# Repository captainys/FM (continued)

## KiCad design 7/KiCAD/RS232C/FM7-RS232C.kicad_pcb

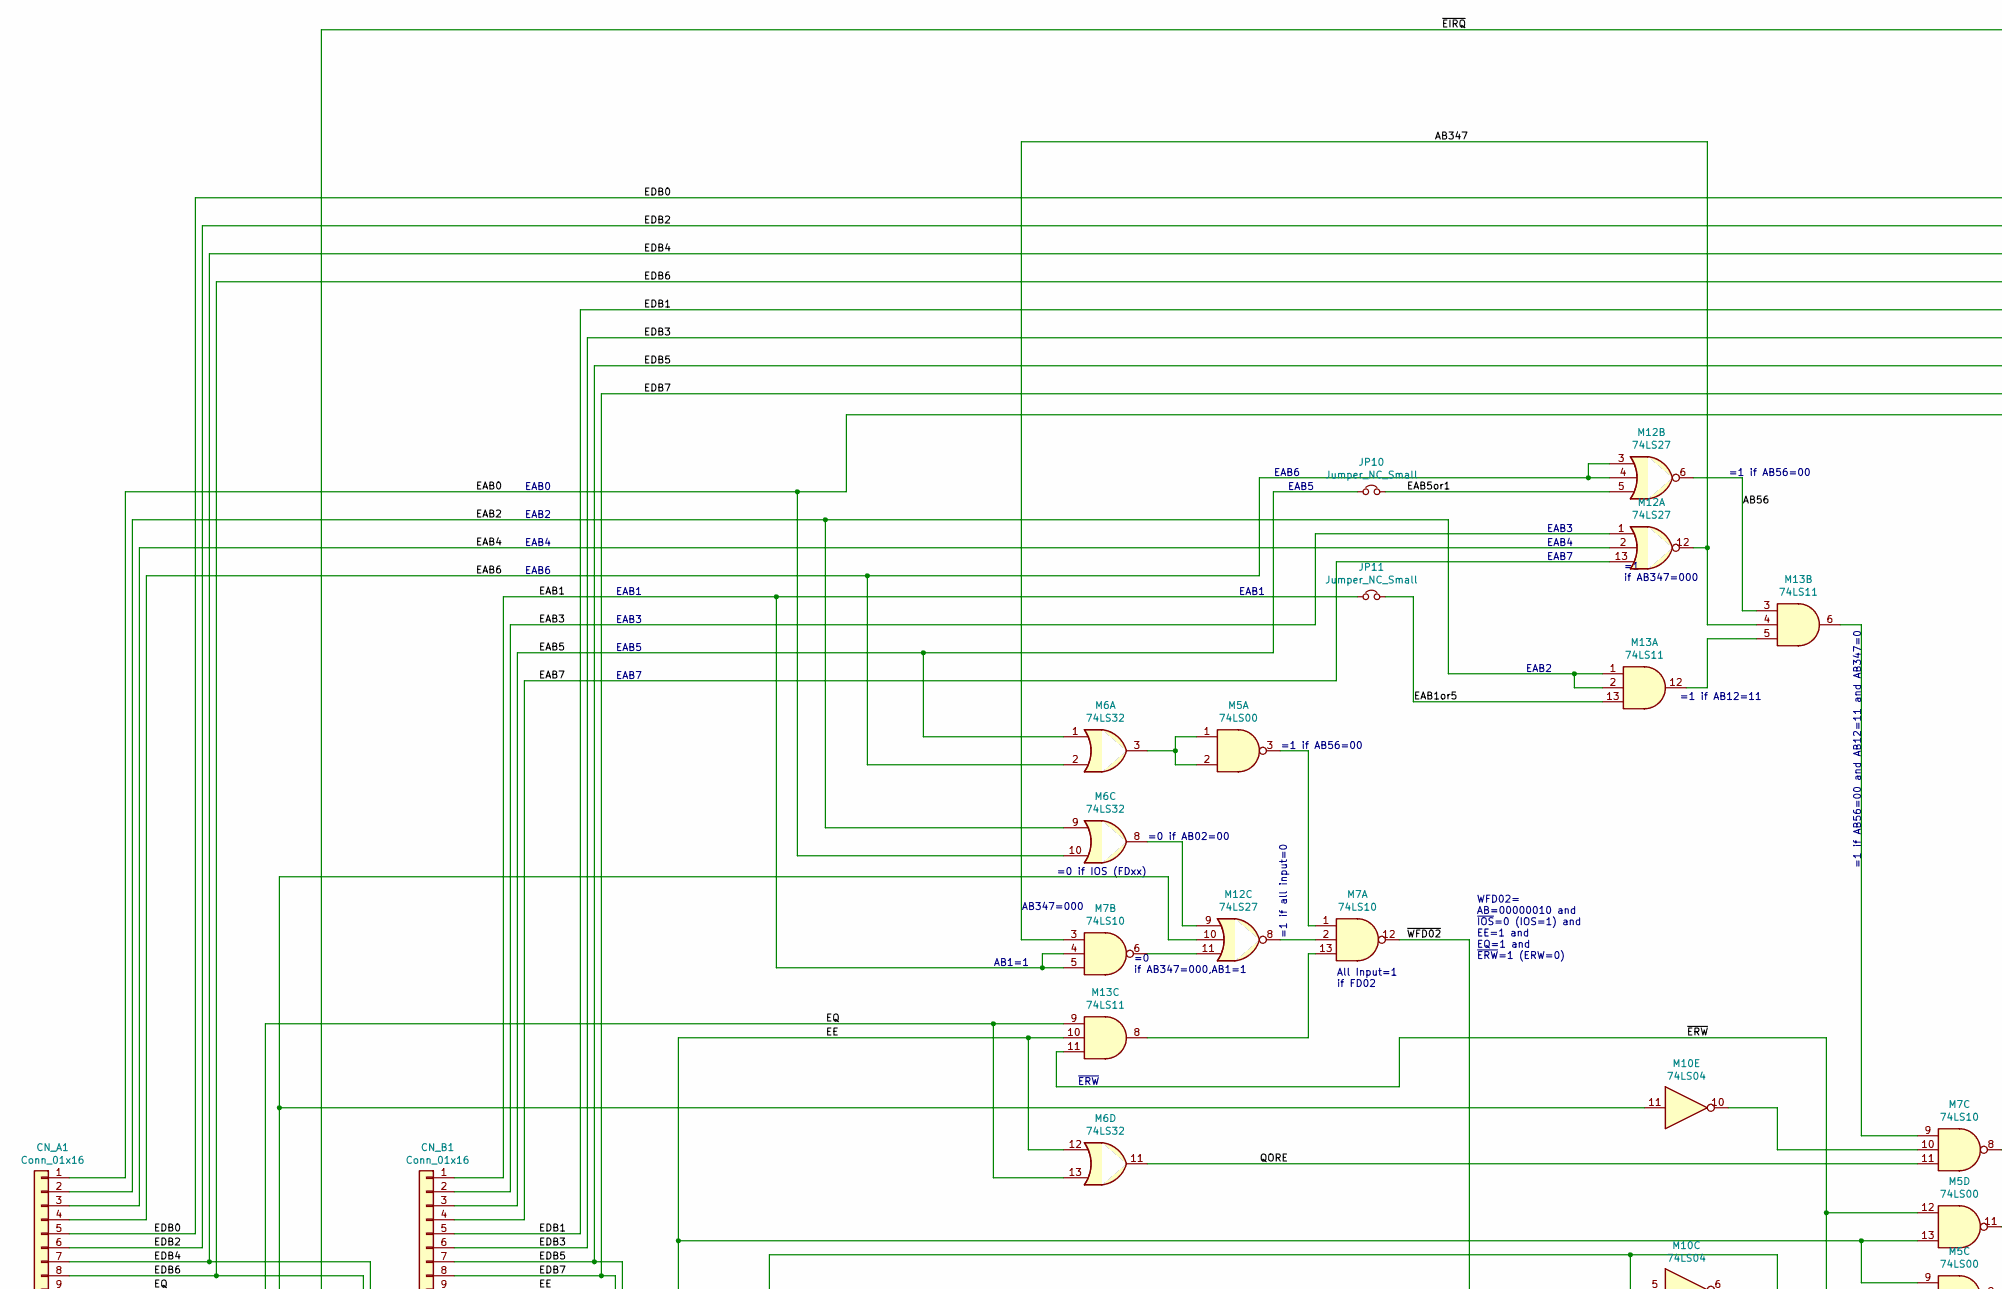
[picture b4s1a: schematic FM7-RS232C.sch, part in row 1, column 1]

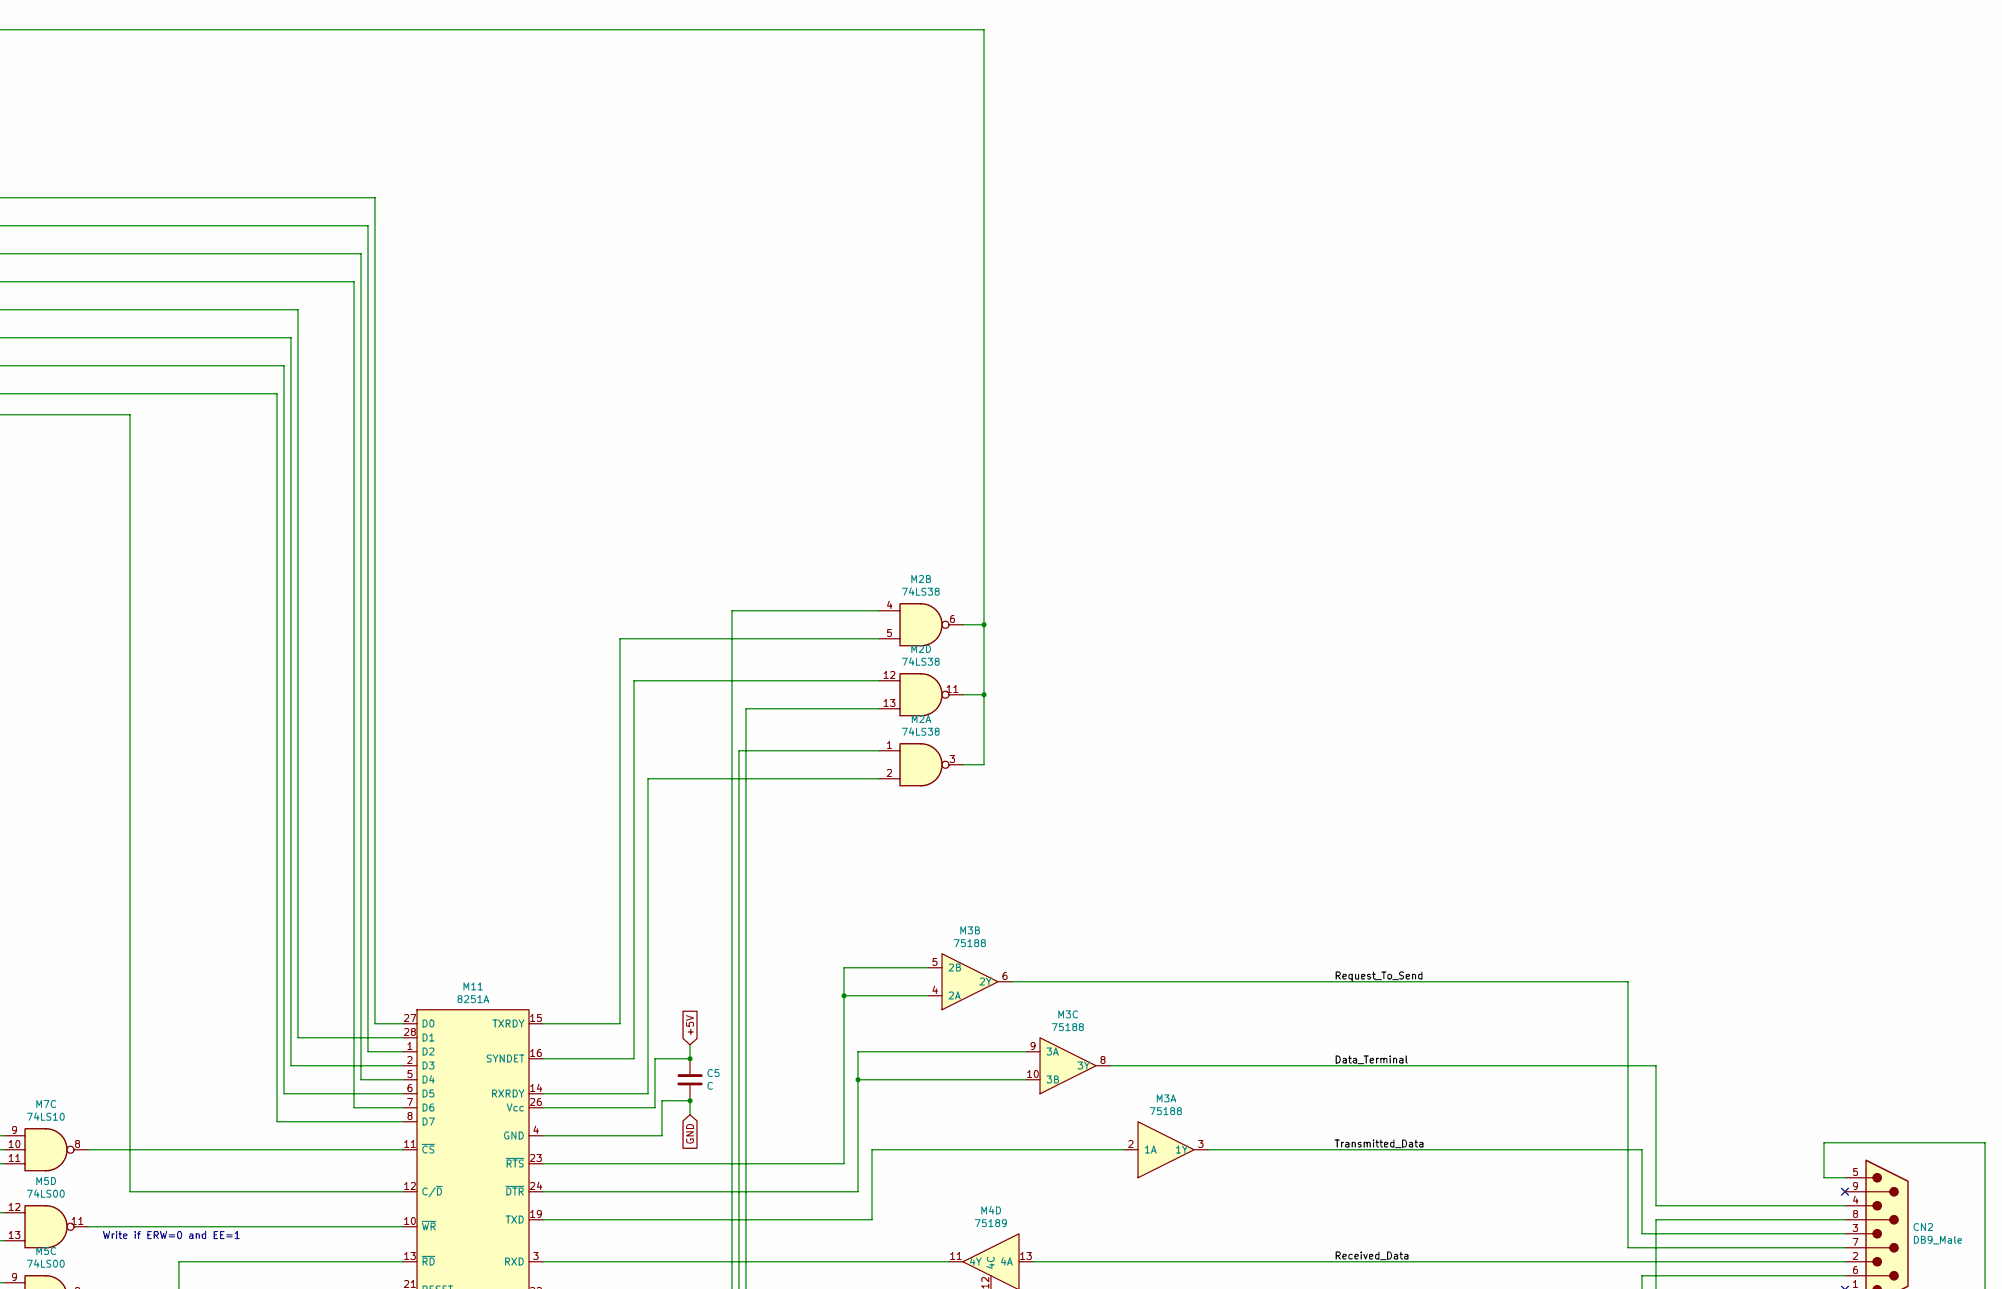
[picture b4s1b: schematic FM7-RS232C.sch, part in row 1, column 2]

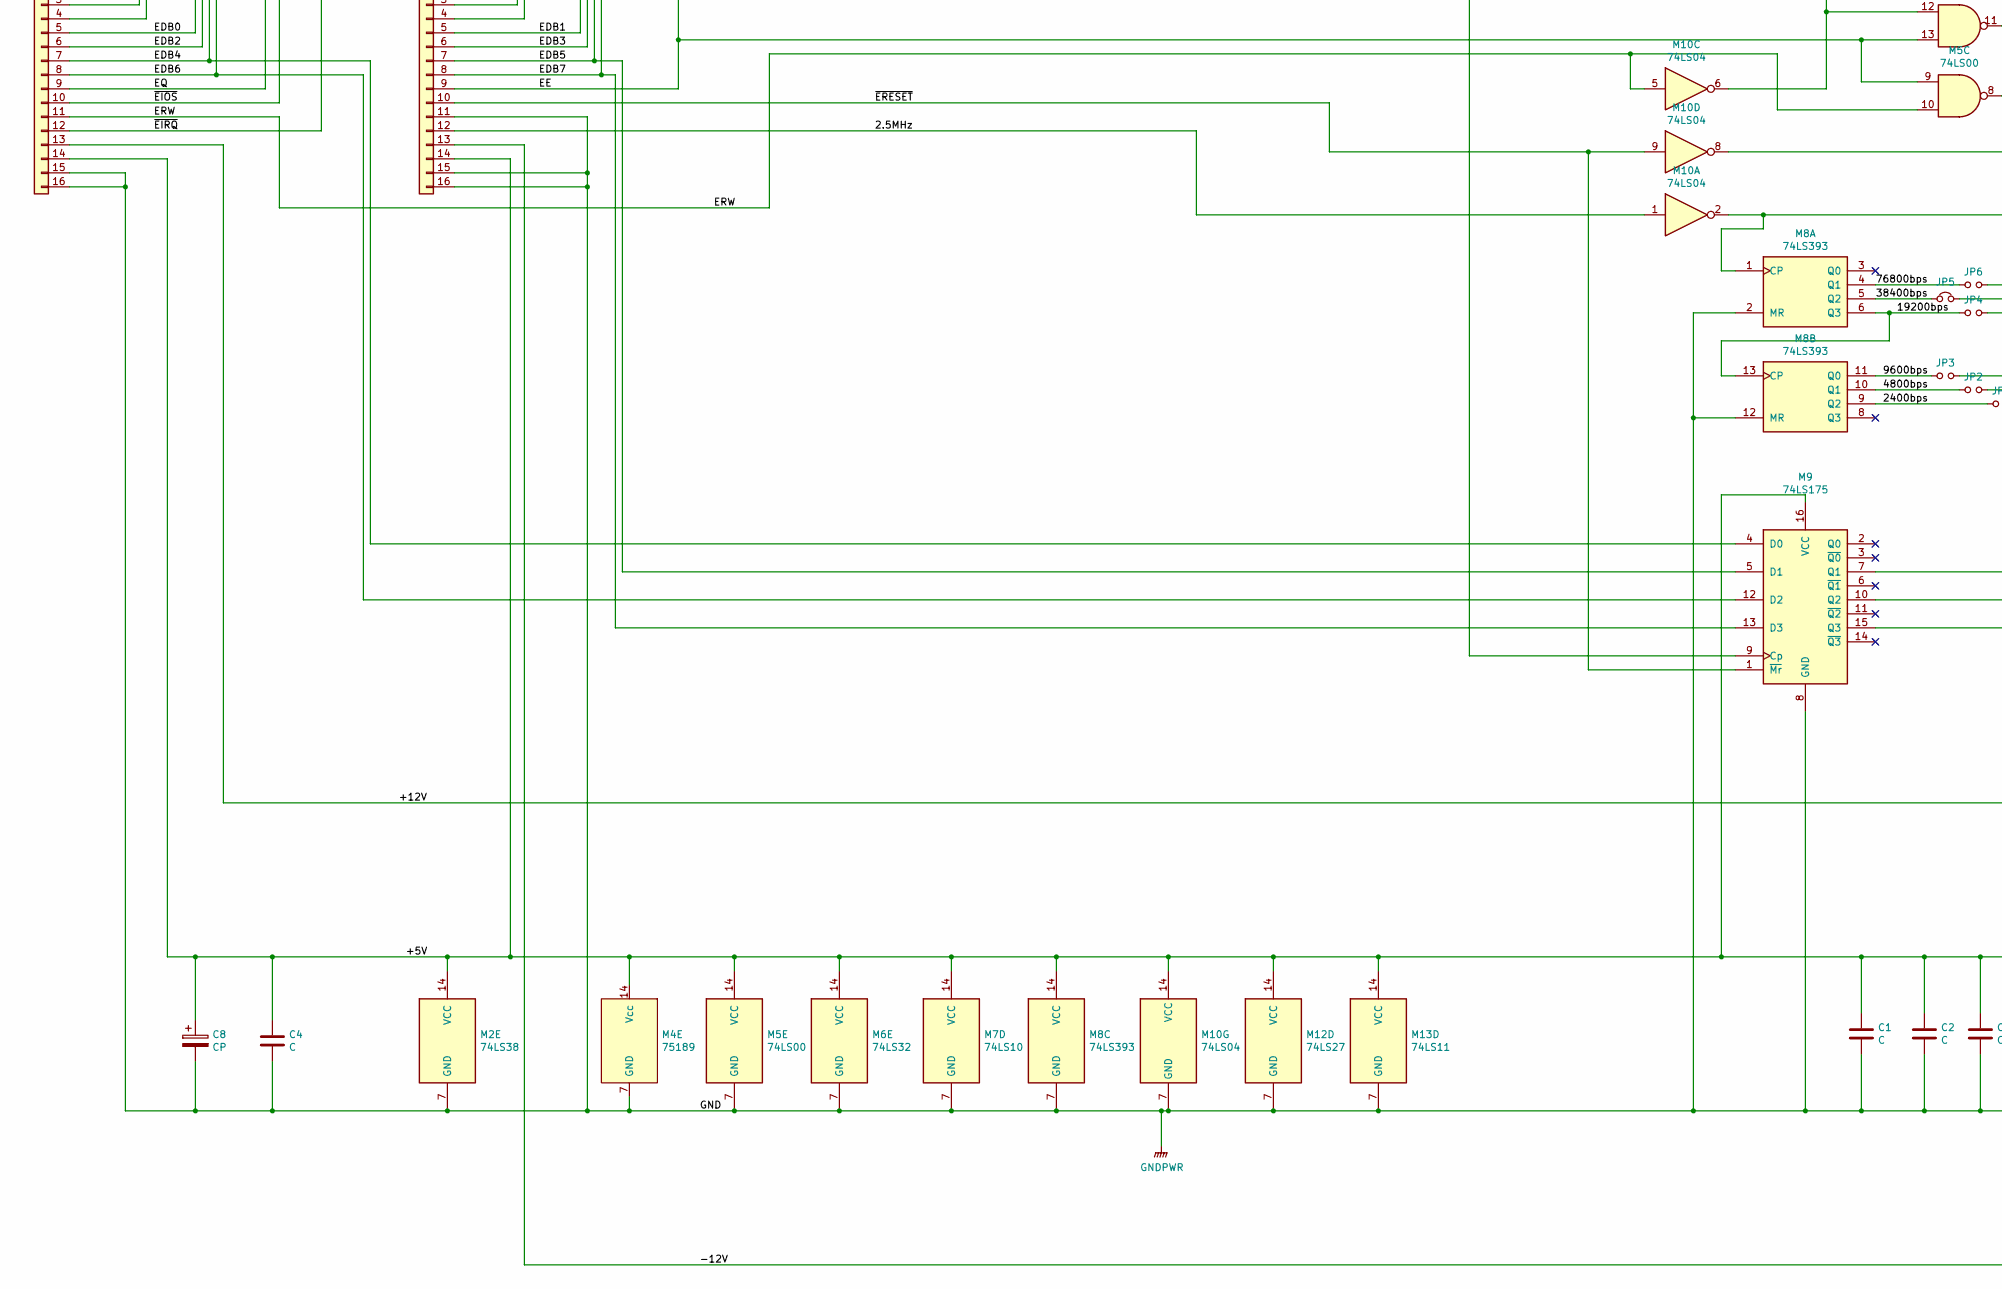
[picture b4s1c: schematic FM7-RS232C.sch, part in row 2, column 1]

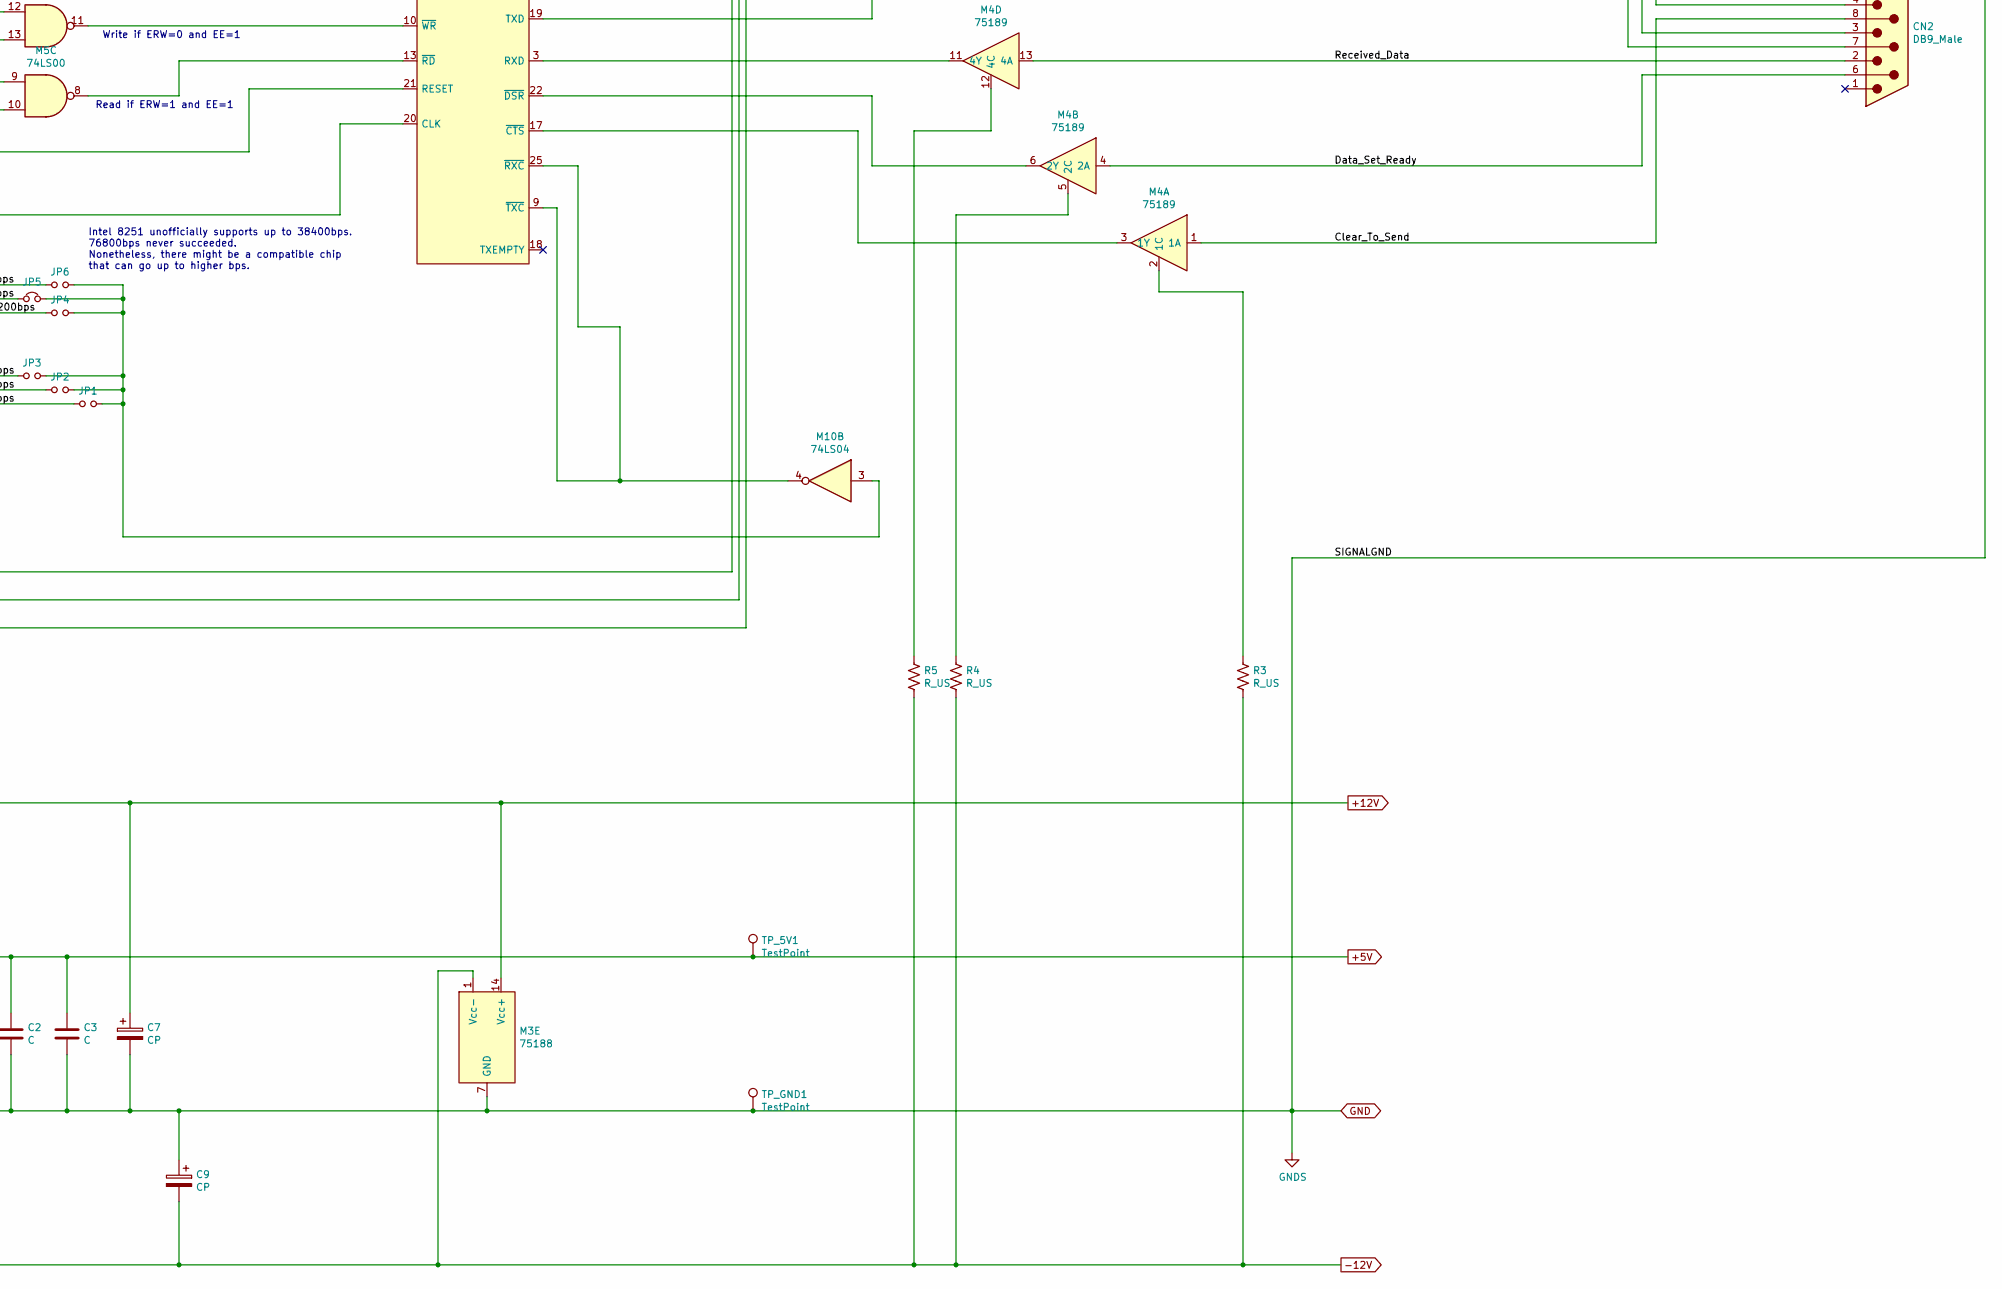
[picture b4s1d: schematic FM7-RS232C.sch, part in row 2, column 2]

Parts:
C1, C2, C3, C4, C5: C; C_Disc_D7.5mm_W5.0mm_P7.50mm
C7, C8, C9: CP; C_Axial_L17.0mm_D6.5mm_P25.00mm_Horizontal
CN2: DB9_Male; DSUB-9_Male_Vertical_P2.77x2.84mm
CN_A1: Conn_01x16; PinHeader_1x16_P2.54mm_Vertical
CN_B1: Conn_01x16; PinHeader_1x16_P2.54mm_Vertical
JP1, JP2, JP3, JP4, JP6: Jumper_NO_Small; PinHeader_1x02_P2.54mm_Vertical
JP5, JP10, JP11: Jumper_NC_Small; PinHeader_1x02_P2.54mm_Vertical
M2: 74LS38; DIP-14_W7.62mm_Socket
M3: 75188; DIP-14_W7.62mm_Socket
M4: 75189; DIP-14_W7.62mm_Socket
M5: 74LS00; DIP-14_W7.62mm_Socket
M6: 74LS32
M7: 74LS10; DIP-14_W7.62mm_Socket
M8: 74LS393; DIP-14_W7.62mm_Socket
M9: 74LS175; DIP-16_W7.62mm_Socket
M10: 74LS04; DIP-14_W7.62mm_Socket
M11: 8251A; DIP-28_W15.24mm_Socket
M12: 74LS27; DIP-14_W7.62mm_Socket
M13: 74LS11; DIP-14_W7.62mm_Socket
R3, R4, R5: R_US; R_Axial_DIN0207_L6.3mm_D2.5mm_P10.16mm_Horizontal
TP_5V1: TestPoint; TestPoint_THTPad_D1.5mm_Drill0.7mm
TP_GND1: TestPoint; TestPoint_THTPad_D1.5mm_Drill0.7mm

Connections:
+5V: C1.1, C2.1, C3.1, C4.1, C5.1, C8.1, CN_A1.14, CN_B1.14, M2.14 (VCC), M4.14 (Vcc), M5.14 (VCC), M6.14 (VCC), M7.14 (VCC), M8.14 (VCC), M9.16 (VCC), M10.14 (VCC), M11.26 (Vcc), M12.14 (VCC), M13.14 (VCC), TP_5V1.1
+12V: C7.1, CN_A1.13, M3.14 (Vcc+)
-12V: C9.2, CN_B1.13, M3.1 (Vcc-), R3.2, R4.2, R5.2
/2.5MHz: CN_B1.12, M10.1
/2400bps: JP1.1, M8.9 (Q2)
/4800bps: JP2.1, M8.10 (Q1)
/9600bps: JP3.1, M8.11 (Q0)
/19200bps: JP4.1, M8.6 (Q3), M8.13 (CP)
/38400bps: JP5.1, M8.5 (Q2)
/76800bps: JP6.1, M8.4 (Q1)
/AB56: M12.6, M13.3
/AB347: M7.3, M12.12, M13.4
/Clear_To_Send: CN2.8, M4.1 (1A)
/Data_Set_Ready: CN2.6, M4.4 (2A)
/Data_Terminal: CN2.4, M3.8 (3Y)
/EAB0: CN_A1.1, M6.10, M11.12 (C/~D)
/EAB1: CN_B1.1, JP11.1, M7.4, M7.5
/EAB1or5: JP11.2, M13.13
/EAB2: CN_A1.2, M6.9, M13.1, M13.2
/EAB3: CN_B1.2, M12.1
/EAB4: CN_A1.3, M12.2
/EAB5: CN_B1.3, JP10.1, M6.1
/EAB5or1: JP10.2, M12.5
/EAB6: CN_A1.4, M6.2, M12.3, M12.4
/EAB7: CN_B1.4, M12.13
/EDB0: CN_A1.5, M11.27 (D0)
/EDB1: CN_B1.5, M11.28 (D1)
/EDB2: CN_A1.6, M11.1 (D2)
/EDB3: CN_B1.6, M11.2 (D3)
/EDB4: CN_A1.7, M9.4 (D0), M11.5 (D4)
/EDB5: CN_B1.7, M9.5 (D1), M11.6 (D5)
/EDB6: CN_A1.8, M9.12 (D2), M11.7 (D6)
/EDB7: CN_B1.8, M9.13 (D3), M11.8 (D7)
/EE: CN_B1.9, M5.9, M5.13, M6.12, M13.10
/EQ: CN_A1.9, M6.13, M13.9
/ERW: CN_A1.11, M5.10, M10.5
/QORE: M6.11, M7.11
/Received_Data: CN2.2, M4.13 (4A)
/Request_To_Send: CN2.7, M3.6 (2Y)
/Transmitted_Data: CN2.3, M3.3 (1Y)
/~EIOS: CN_A1.10, M10.11, M12.10
/~EIRQ: CN_A1.12, M2.3, M2.6, M2.11
/~ERESET: CN_B1.10, M9.1 (~Mr), M10.9
/~ERW: M5.12, M10.6, M13.11
/~WFD02: M7.12, M9.9 (Cp)
GND: C1.2, C2.2, C3.2, C4.2, C5.2, C7.2, C8.2, C9.1, CN2.5, CN_A1.15, CN_A1.16, CN_B1.11, CN_B1.15, CN_B1.16, M2.7 (GND), M3.7 (GND), M4.7 (GND), M5.7 (GND), M6.7 (GND), M7.7 (GND), M8.2 (MR), M8.7 (GND), M8.12 (MR), M9.8 (GND), M10.7 (GND), M11.4 (GND), M12.7 (GND), M13.7 (GND), TP_GND1.1
unnamed: JP1.2, JP2.2, JP3.2, JP4.2, JP5.2, JP6.2, M10.3
unnamed: M2.1, M9.10 (Q2)
unnamed: M2.4, M9.7 (Q1)
unnamed: M2.13, M9.15 (Q3)
unnamed: M4.2 (1C), R3.1
unnamed: M4.5 (2C), R4.1
unnamed: M4.12 (4C), R5.1
unnamed: M5.1, M5.2, M6.3
unnamed: M5.3, M7.1
unnamed: M8.1 (CP), M10.2, M11.20 (CLK)
unnamed: M10.4, M11.9 (~TXC), M11.25 (~RXC)
unnamed: M10.8, M11.21 (RESET)
unnamed: M7.10, M10.10
unnamed: M4.11 (4Y), M11.3 (RXD)
unnamed: M5.11, M11.10 (~WR)
unnamed: M7.8, M11.11 (~CS)
unnamed: M5.8, M11.13 (~RD)
unnamed: M2.2, M11.14 (RXRDY)
unnamed: M2.5, M11.15 (TXRDY)
unnamed: M2.12, M11.16 (SYNDET)
unnamed: M4.3 (1Y), M11.17 (~CTS)
unnamed: M3.2 (1A), M11.19 (TXD)
unnamed: M4.6 (2Y), M11.22 (~DSR)
unnamed: M3.4 (2A), M3.5 (2B), M11.23 (~RTS)
unnamed: M3.9 (3A), M3.10 (3B), M11.24 (~DTR)
unnamed: M7.2, M12.8
unnamed: M6.8, M12.9
unnamed: M7.6, M12.11
unnamed: M7.9, M13.6
unnamed: M7.13, M13.8
unnamed: M13.5, M13.12

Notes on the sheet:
EAB0
EAB2
EAB4
EAB6
EAB1
EAB3
EAB5
EAB7
AB347=000
AB1=1
=0 if AB02=00
=0 if IOS (FDxx)
All Input=1 if FD02
=1 if AB56=00
=1 if AB347=000
=1 if AB12=11
=1 if all input=0
=1 if AB56=00 and AB12=11 and AB347=0
WFD02= AB=00000010 and ~IOS~=0 (IOS=1) and EE=1 and EQ=1 and ~ERW~=1 (ERW=0)
Read if ERW=1 and EE=1
Write if ERW=0 and EE=1
Intel 8251 unofficially supports up to 38400bps. 76800bps never succeeded. Nonetheless, there might be a compatible chip that can go up to higher bps.
=0 if AB347=000,AB1=1
~ERW

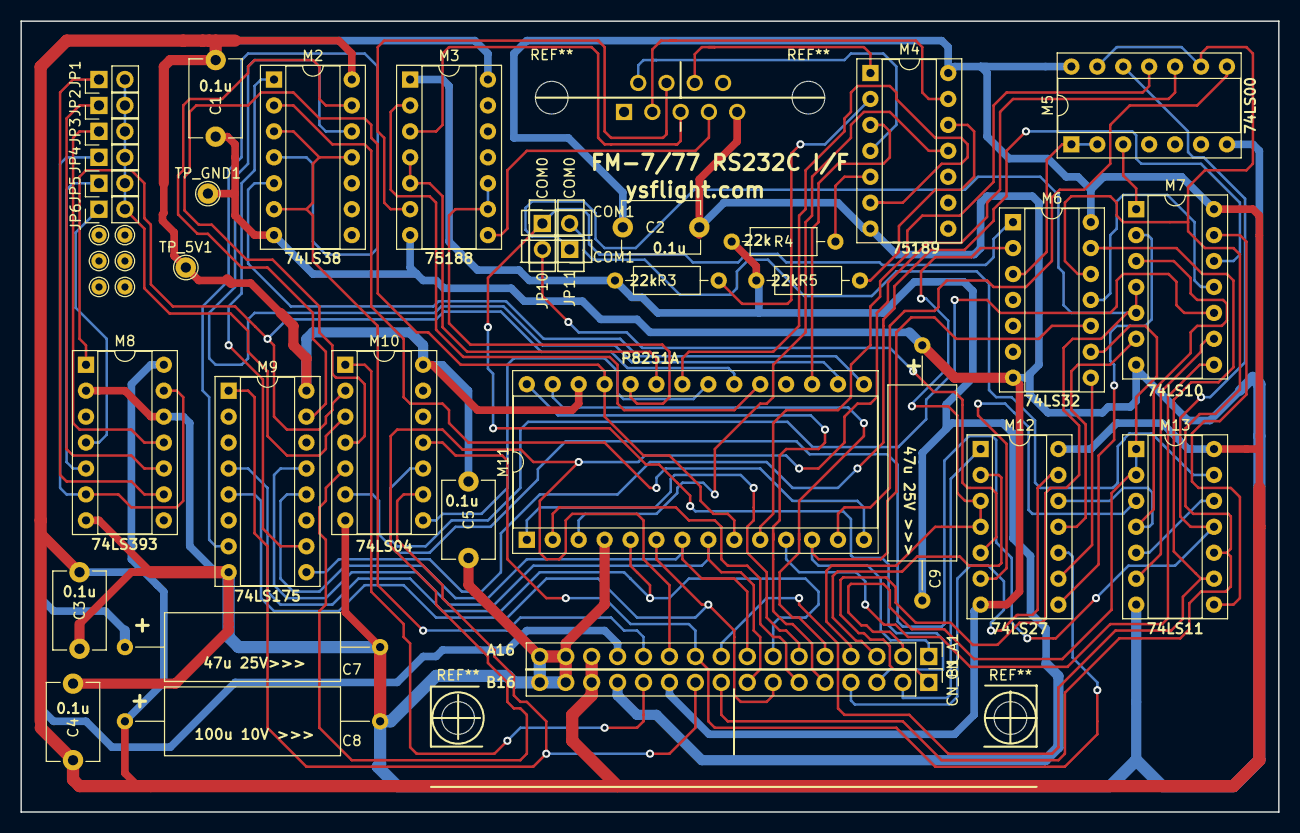
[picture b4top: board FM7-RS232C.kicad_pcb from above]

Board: 2 copper layers, 123.2 x 77.5 mm, 36 parts (1 on the bottom side), 77 nets.

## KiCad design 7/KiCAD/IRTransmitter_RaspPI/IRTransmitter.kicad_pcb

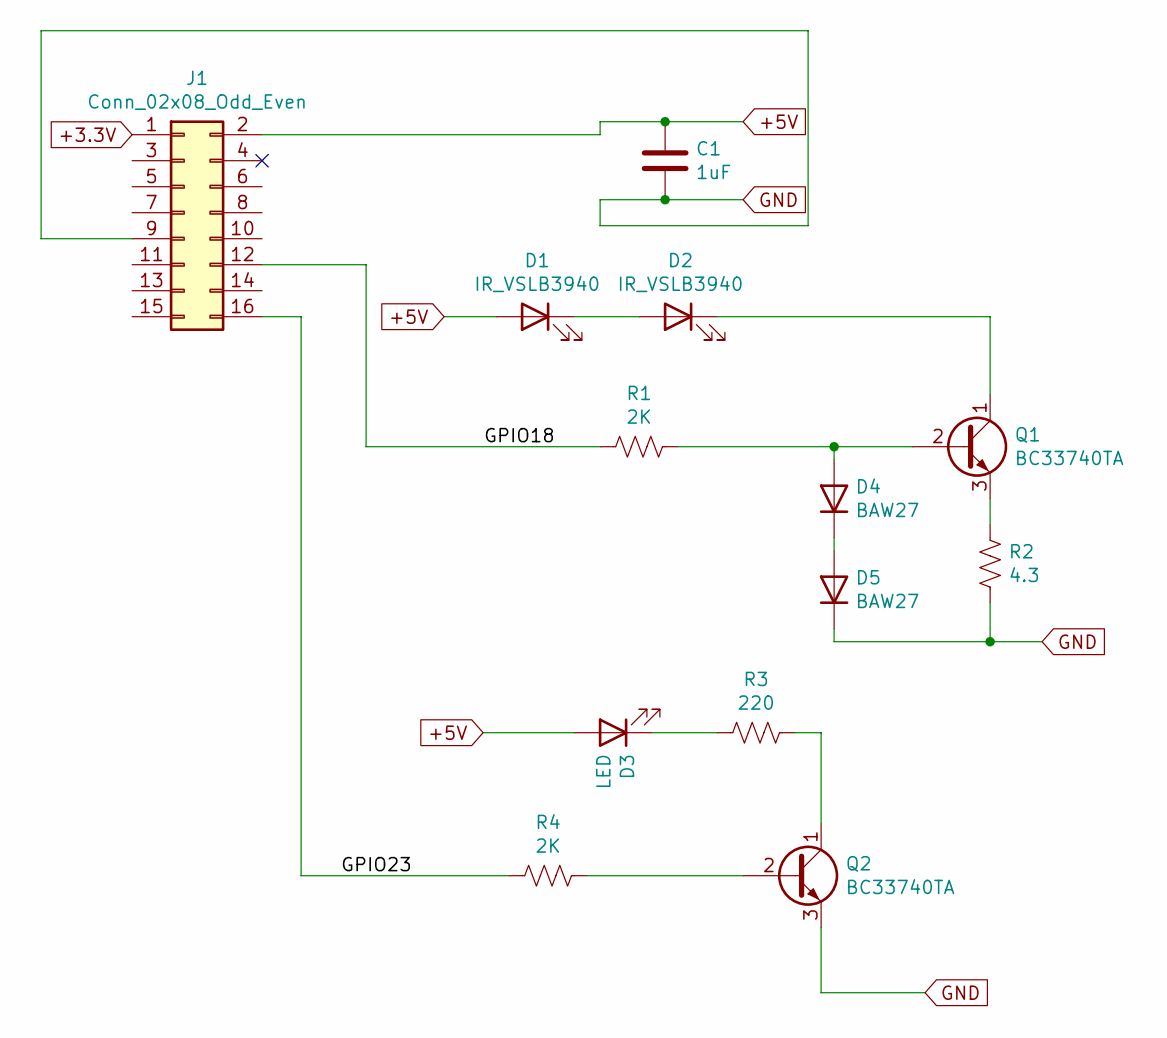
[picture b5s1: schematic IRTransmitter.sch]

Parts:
C1: 1uF; C_Disc_D4.3mm_W1.9mm_P5.00mm
D1, D2: IR_VSLB3940; LED_D5.0mm
D3: LED; LED_D5.0mm
D4, D5: BAW27; D_T-1_P10.16mm_Horizontal
J1: Conn_02x08_Odd_Even; PinHeader_2x08_P2.54mm_Vertical
Q1, Q2: BC33740TA; NPN_Transistor
R1, R4: 2K; R_Axial_DIN0207_L6.3mm_D2.5mm_P10.16mm_Horizontal
R2: 4.3; R_Axial_DIN0207_L6.3mm_D2.5mm_P10.16mm_Horizontal
R3: 220; R_Axial_DIN0207_L6.3mm_D2.5mm_P10.16mm_Horizontal

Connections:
+3.3V: J1.1
+5V: C1.1, D1.2 (A), D3.2 (A), J1.2
/GPIO18: J1.12, R1.2
/GPIO23: J1.16, R4.2
GND: C1.2, D5.1 (K), J1.9, Q2.3 (E), R2.2
unnamed: D1.1 (K), D2.2 (A)
unnamed: D2.1 (K), Q1.1 (C)
unnamed: D3.1 (K), R3.2
unnamed: D4.1 (K), D5.2 (A)
unnamed: D4.2 (A), Q1.2 (B), R1.1
unnamed: Q1.3 (E), R2.1
unnamed: Q2.1 (C), R3.1
unnamed: Q2.2 (B), R4.1

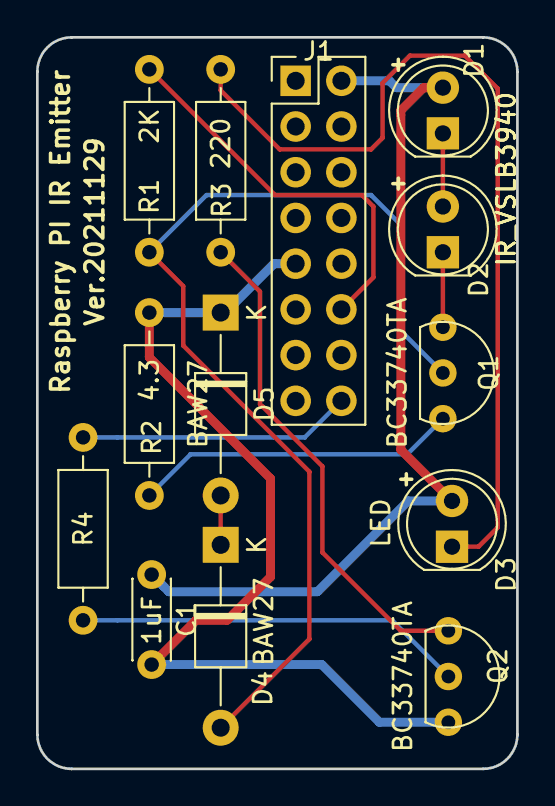
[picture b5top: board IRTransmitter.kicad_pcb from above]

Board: 2 copper layers, 26.7 x 40.6 mm, 13 parts (0 on the bottom side), 12 nets.

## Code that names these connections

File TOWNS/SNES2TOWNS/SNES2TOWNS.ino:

/* LICENSE>>
Copyright 2023 Soji Yamakawa (CaptainYS, http://www.ysflight.com)

Redistribution and use in source and binary forms, with or without modification, are permitted provided that the following conditions are met:

1. Redistributions of source code must retain the above copyright notice, this list of conditions and the following disclaimer.

2. Redistributions in binary form must reproduce the above copyright notice, this list of conditions and the following disclaimer in the documentation and/or other materials provided with the distribution.

3. Neither the name of the copyright holder nor the names of its contributors may be used to endorse or promote products derived from this software without specific prior written permission.

THIS SOFTWARE IS PROVIDED BY THE COPYRIGHT HOLDERS AND CONTRIBUTORS "AS IS" AND ANY EXPRESS OR IMPLIED WARRANTIES, INCLUDING, BUT NOT LIMITED TO, THE IMPLIED WARRANTIES OF MERCHANTABILITY AND FITNESS FOR A PARTICULAR PURPOSE ARE DISCLAIMED. IN NO EVENT SHALL THE COPYRIGHT HOLDER OR CONTRIBUTORS BE LIABLE FOR ANY DIRECT, INDIRECT, INCIDENTAL, SPECIAL, EXEMPLARY, OR CONSEQUENTIAL DAMAGES (INCLUDING, BUT NOT LIMITED TO, PROCUREMENT OF SUBSTITUTE GOODS OR SERVICES; LOSS OF USE, DATA, OR PROFITS; OR BUSINESS INTERRUPTION) HOWEVER CAUSED AND ON ANY THEORY OF LIABILITY, WHETHER IN CONTRACT, STRICT LIABILITY, OR TORT (INCLUDING NEGLIGENCE OR OTHERWISE) ARISING IN ANY WAY OUT OF THE USE OF THIS SOFTWARE, EVEN IF ADVISED OF THE POSSIBILITY OF SUCH DAMAGE.

<< LICENSE */


#include <avr/sleep.h>


// Based on:
// https://forum.arduino.cc/t/help-needed-sleeping-the-atmega4809-arduino-nano-every/914000/2
// http://ww1.microchip.com/downloads/en/AppNotes/TB3213-Getting-Started-with-RTC-90003213A.pdf


#define USE_RTC



#define AS_TOWNS2BTN 14  // If A0 is high, present self as 2-Button Towns Game Pad
#define AS_TOWNS6BTN 15  // If A1 is high, present self as 6-Button Towns Game Pad
#define CLOCK 17  // A0 for CLOCK
#define LATCH 18  // A1 for LATCH
#define DATA 19   // A2 for DATA


// Order SNES game pad sends.
#define _B 0
#define _Y 1
#define _SELECT 2
#define _START 3
#define _UP 4
#define _DOWN 5
#define _LEFT 6
#define _RIGHT 7
#define _A 8
#define _X 9
#define _L 10
#define _R 11

//                   CPSF     TOWNS 6BTN    TOWNS 2BTN
#define OUT_P1A 16  // UP          UP            UP
#define OUT_P1B 12  // R           X             UP
#define OUT_P2A 11  // DOWN        DOWN          DOWN
#define OUT_P2B 10  // Y           Y             DOWN
#define OUT_P3A  9  // LEFT        LEFT          LEFT
#define OUT_P3B  8  // X           L             LEFT
#define OUT_P4A  7  // RIGHT       RIGHT         RIGHT
#define OUT_P4B  6  // SEL         R             RIGHT
#define OUT_P6A  5  // A           A             A
#define OUT_P6B  4  // L           A             A
#define OUT_P7A  3  // B           B             B
#define OUT_P7B  2  // START       B             B

#define NUM_OUTPUTS 12
#define SNES_NUM_PULSES 16

void setup() {
  unsigned int out_pins[NUM_OUTPUTS]=
  {
    OUT_P1A,
    OUT_P1B,
    OUT_P2A,
    OUT_P2B,
    OUT_P3A,
    OUT_P3B,
    OUT_P4A,
    OUT_P4B,
    OUT_P6A,
    OUT_P6B,
    OUT_P7A,
    OUT_P7B,
  };

  pinMode(LATCH, OUTPUT);
  pinMode(CLOCK, OUTPUT);
  pinMode(DATA, INPUT);

  pinMode(LED_BUILTIN,OUTPUT);
  digitalWrite(LED_BUILTIN,LOW);

  digitalWrite(CLOCK, LOW);
  digitalWrite(LATCH, LOW);

  for(int i=0; i<NUM_OUTPUTS; ++i) {
    pinMode(out_pins[i], OUTPUT);
    digitalWrite(out_pins[i], LOW);
  }

  pinMode(AS_TOWNS2BTN, INPUT);
  pinMode(AS_TOWNS6BTN, INPUT);

#ifdef USE_RTC
  while(RTC.STATUS>0);
  RTC.CLKSEL=RTC_CLKSEL_INT32K_gc; // 32K Hz Oscillator
  RTC.PITINTCTRL=RTC_PI_bm;           // Periodic Interrupt
  RTC.PITCTRLA=RTC_PERIOD_CYC512_gc|RTC_PITEN_bm;  // Roughly every 16ms
  set_sleep_mode(SLEEP_MODE_PWR_DOWN);
  sleep_enable();
#endif
}

enum
{
  MODE_AS_CPSF,
  MODE_AS_TOWNS6BUTTON,
  MODE_AS_TOWNSPAD,
};

void DoTownsThings(unsigned int readbuf[])
{
  if(LOW==readbuf[_SELECT])
  {
    readbuf[_UP]=LOW;
    readbuf[_DOWN]=LOW;
  }
  if(LOW==readbuf[_START])
  {
    readbuf[_LEFT]=LOW;
    readbuf[_RIGHT]=LOW;
  }
}

void UpdateController(void)
{
  unsigned int readbuf[NUM_OUTPUTS];
  unsigned int mode=MODE_AS_CPSF;
  if(HIGH==digitalRead(AS_TOWNS2BTN))
  {
    mode=MODE_AS_TOWNSPAD;
  }
  else if(HIGH==digitalRead(AS_TOWNS6BTN))
  {
    mode=MODE_AS_TOWNS6BUTTON;
  }

  digitalWrite(CLOCK, HIGH);
  digitalWrite(LATCH, HIGH);
  delayMicroseconds(12);
  digitalWrite(LATCH, LOW);
  // Experiment indicates 16 clock pulses are necessary for SNES Controller.
  // CAPCOM Power Stick Fighter works fine if I stop at 12 clock pulses, but
  // SNES Controller occasionally fails to latch if I do not cycle clock pulse 16 times after latch.
  // Update: SNES Controller apparently does not allow re-latching until all 16 clock pulses comes.
  //         Therefore, if I stop reading at 12 clock pulses, next time the latch pulse is ignored,
  //         and I only reads left-over four bits, which are not assigned to any buttons.
  //         This behavior is not observed in CAPCOM Power Stick Fighter.
  for (int i = 0; i<SNES_NUM_PULSES; ++i) {
    delayMicroseconds(6);
    if(i<NUM_OUTPUTS)
    {
      readbuf[i]=digitalRead(DATA);
    }
    digitalWrite(CLOCK, LOW);
    delayMicroseconds(6);
    digitalWrite(CLOCK, HIGH);
  }

  switch(mode)
  {
  case MODE_AS_CPSF:
    digitalWrite(OUT_P1A,readbuf[_UP]);
    digitalWrite(OUT_P1B,readbuf[_R]);
    digitalWrite(OUT_P2A,readbuf[_DOWN]);
    digitalWrite(OUT_P2B,readbuf[_Y]);
    digitalWrite(OUT_P3A,readbuf[_LEFT]);
    digitalWrite(OUT_P3B,readbuf[_X]);
    digitalWrite(OUT_P4A,readbuf[_RIGHT]);
    digitalWrite(OUT_P4B,readbuf[_SELECT]);
    digitalWrite(OUT_P6A,readbuf[_A]);
    digitalWrite(OUT_P6B,readbuf[_L]);
    digitalWrite(OUT_P7A,readbuf[_B]);
    digitalWrite(OUT_P7B,readbuf[_START]);
    break;
  case MODE_AS_TOWNS6BUTTON:
    DoTownsThings(readbuf);
    digitalWrite(OUT_P1A,readbuf[_UP]);
    digitalWrite(OUT_P1B,readbuf[_X]);
    digitalWrite(OUT_P2A,readbuf[_DOWN]);
    digitalWrite(OUT_P2B,readbuf[_Y]);
    digitalWrite(OUT_P3A,readbuf[_LEFT]);
    digitalWrite(OUT_P3B,readbuf[_L]);
    digitalWrite(OUT_P4A,readbuf[_RIGHT]);
    digitalWrite(OUT_P4B,readbuf[_R]);
    digitalWrite(OUT_P6A,readbuf[_A]);
    digitalWrite(OUT_P6B,readbuf[_A]);
    digitalWrite(OUT_P7A,readbuf[_B]);
    digitalWrite(OUT_P7B,readbuf[_B]);
    break;
  case MODE_AS_TOWNSPAD:
    DoTownsThings(readbuf);
    digitalWrite(OUT_P1A,readbuf[_UP]);
    digitalWrite(OUT_P1B,readbuf[_UP]);
    digitalWrite(OUT_P2A,readbuf[_DOWN]);
    digitalWrite(OUT_P2B,readbuf[_DOWN]);
    digitalWrite(OUT_P3A,readbuf[_LEFT]);
    digitalWrite(OUT_P3B,readbuf[_LEFT]);
    digitalWrite(OUT_P4A,readbuf[_RIGHT]);
    digitalWrite(OUT_P4B,readbuf[_RIGHT]);
    digitalWrite(OUT_P6A,readbuf[_A]);
    digitalWrite(OUT_P6B,readbuf[_A]);
    digitalWrite(OUT_P7A,readbuf[_B]);
    digitalWrite(OUT_P7B,readbuf[_B]);
    break;
  }
}

#ifdef USE_RTC
unsigned char counter=0;

ISR(RTC_PIT_vect)
{
  counter=(counter+1)&63;
  if(0==counter)
  {
    digitalWrite(LED_BUILTIN,HIGH);
  }

  UpdateController();
  RTC.PITINTFLAGS = RTC_PI_bm;  // Is it required?  The sample says so.

  if(0==counter)
  {
    digitalWrite(LED_BUILTIN,LOW);
  }
}
void loop() {
  sleep_cpu();
}
#else
void loop() {
  UpdateController();
}
#endif

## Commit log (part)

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2022-05-05 Updated binary.
2022-05-05 Fixed wrong menu count in non-ICM boot.
2022-05-06 Fixed Boot Device Menu item count.
2022-05-06 Added CONS31K.COM, run this program to reset CRTC in 31KHz mode in command mode.
2022-05-06 Rescue IPL forces starting console to be 31KHz.
2022-05-06 CMOS Menu and Boot Drive Menu was not waiting for pad release.
2022-05-07 Added DMCD (Dump CD Sectors)
2022-05-07 Gave up reading 2340 bytes per sector. I doubt if Towns' CD-ROM BIOS really could do it.
2022-05-08 Embedded YSSCSICD.SYS in LOADER
2022-05-09 Cutting down size of YSSCSICD.SYS
2022-05-09 Added write verification in ICMWRITE.
2022-05-09 Re-instating BOOTSECT
2022-05-10 Updated FRAM card schematic and PCB. Added pull-up resistors for ~CE1 and ~CE2 to prevent data corruption on hog-plug and hot-unplug.
2022-05-10 Fixed an artifact.
2022-05-11 Disk BIOS fails to recognize memory card for the first write, when all bytes are zero. Probably it is trying to look at REG memory, but FRAM card omits REG memory to save cost. Instead, ICMWRITE.EXP 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
2022-05-11 ICM records CMOS-BackedUp flag at C000DFFFH. ICMWRITE.EXP has an option to just write leaving backed-up CMOS, or clear and write.
2022-05-11 Updated the version number.
2022-05-14 Added logic OR for better write protection.
2022-05-14 Switching to KiCad 6.0
2022-05-17 Added OR-gate to enforce Write Protection.
2022-05-20 Working on PCB for NX1 PCMCIA frame.
2022-05-20 Added fillet
2022-05-20 Cleaning up PCB
2022-05-21 Updating PCB bare version.
2022-05-21 Moved ~CE1, ~CE2 pull-up resistors closer to the FRAM chip.
2022-05-23 Cleaning up vias.
2022-05-23 Moving files around
2022-05-26 Simplifying PCB
2022-06-03 Updated version number
2022-07-22 Trying to detect unstable bytes from multiple reads.
2022-07-23 Temporarily disabled unstable-byte finder.
2022-07-23 Increased re-read count to 16.
2022-07-23 Fixed Read Size. Drive 0 to 1 continuous mode in RAWREAD
2022-07-23 Bug Fix
2022-07-25 Updating RAWREAD so that it can use ext RAM of FM77AV.
2022-07-25 TRANSMIT_SECTOR_DUMP was not masking IRQs.
2022-07-26 RAWREAD was not waiting for TxEMPTY after sending sector dump. The program was tested fine on Mutsu, but not on actual FM77AV. RAWREAD now waits for TxEMPTY after transmitting sector dump, and works 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
2022-10-14 Synched
2022-10-14 Deal with unformatted track.
2022-10-31 Added Franken command.
2022-11-01 Still getting lost-data error, and waits incredibly long on an unformatted track. (Timer condition ignored?)
2022-11-01 Add ASM.ASM
2022-11-02 Tried to use IRR to see FDC IRQ, which failed in real TOWNS.
2022-11-02 Still fails.
2022-11-02 MAKED77 correctly handles unfromat tracks.
2022-11-04 Tried PIC polling mode. It detected IRR, but still fails.
2022-11-05 Tried to take over INT 46H. Failed again. DOS|Extender sucks.
2022-11-05 Working on FDDUMP.
2022-11-05 Temporary copied failed maked77.c here.
2022-11-05 FDDUMP Read Address works ok on the emulator, locks up on real TOWNS
2022-11-07 Read Sector freezes if I want to save RDD file.
2022-11-07 Track-image
2022-11-07 Deal with CRC error more correctly.
2022-11-08 Removed one warning.
2022-11-08 Default last track for 2D, 2DD, and 2HD to 40, 80, and 80 respectively.
2022-11-08 Increased time out. Added sector-read time out.
2022-11-09 Somehow made it work.
2022-11-09 FDDUMP
2022-11-09 Working on RDD2D77
2022-11-09 Added executables.
2022-11-09 Let it scan an additional track by default.
2022-11-09 Added readme for FDDUMP.EXE
2022-11-09 Added message.
2022-11-09 Hope this can capture leaf-in-the-forest protect.
2022-11-10 I don't know if it makes a difference, but I masked timer interrupt at the beginning of FDDUMP.EXE
2022-11-10 Increased the drive-ready wait time.
2022-11-11 Changed the way to check drive ready.
2022-11-12 Added -log option in FDDUMP.
2022-11-13 FDDUMP stores sector flags correctly.
2022-11-21 Working on RDD support.
2022-11-22 Adding .RDD support.
2022-11-22 Fixed crash.
2022-11-22 Forgot adding kicad_mod?
2022-11-23 Updated unstable-byte identification.
2022-11-25 Fixed build.
2022-12-14 Added short cuts in FM77AV Keyboard Emulator.
2023-01-01 Fixing FM77AV Keyboard Emulator.
2023-01-04 Call gpioTerminate on close.
2023-01-23 D77File::SetRawBinary correctly sets media type.
2023-04-05 REALDUMP and REALFIND (dump real-mode-memory and find-in-real-mode-memory.)
2023-08-16 Fix broken build.
2023-08-30 SNES GamePad to TOWNS project.
2023-08-30 SNES to TOWNS Controller Adapter
2023-08-30 Prep for toggle switch.
2023-08-31 Making SNES connector footprint.
2023-08-31 PCB version will be for Arduino NANO.
2023-09-01 First success in reading CPSF from Arduino.
2023-09-01 Changed registers and capacitors from THT to SMD.
2023-09-01 Design Change
2023-09-02 SNES connector footprint.
2023-09-03 Updated PCB from Schematic
2023-09-03 Optimizing PCB
2023-09-03 Updated PCB markings.
2023-09-06 Start button to status LED.
2023-09-07 Fixed Arduino code to support original SNES controllers.
2023-09-07 Added license terms.
2023-09-10 Read controller status every 1/16 seconds to save power consumption.
2023-09-10 Gave up status LED.
2023-09-19 SNES2TOWNS update.
2023-10-02 Updating PCB
2023-10-22 Added comments.
2023-10-27 Supporting unstable-byte flags in RDD.
2023-11-05 Added AD-D15NE Equivalent.
2023-11-05 Updated video adapter PCB.
2023-11-05 Rescue IPL clears COM out to support some MSX joysticks and CPSF.
2023-11-12 Fixed error in FDDUMP in capturing ID marks.
2023-11-12 REPAIRRDD command.
2023-11-13 Exploring possibility of FDDUMP.EXP
2023-11-14 FDDUMP.EXP runs on Tsugaru.
2023-11-14 Change in .RDD spec. Size of unstable-byte flags is offset +E and +F of the tag. It was initially +1 and +2, but there is not supposed to be any .RDD with 10H tag at the time of change. Hopefully it 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
2023-11-18 Fixing RDD-write.
2023-11-18 FDDUMP was not quite correctly measuring sector-read-time. It happend to be close enough in the real-mode version, but not that lucky in the protected-mode version.
2023-11-18 -writeprotect option for FDDUMP.EXP.
2023-11-19 Changed stable-byte id from 4 same bytes in a row to 18 same bytes in a row.
2023-11-19 More RDD integrity check in REPAIRRDD.EXE.
2023-11-21 Moving lines around.
2023-11-21 Buffered write.
2023-11-22 Optimizing
2023-11-23 Fixed D77 encoding.
2023-11-25 Successfully sent keyboard signal via Arduino over wired connection.
2023-11-25 Arduino-based FM77AV Keyboard Emulator starts into the terminal mode, in which the host computer can connect to the Arduino COM port with a conventional serial terminal such as TeraTerm at 115200bps.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
2023-11-25 Unified IREmitter and wired-version of FM77AV Keyboard Emulator.
2023-11-26 Terminal mode supports arrow, del, and ins keys.
2023-12-04 High-Res PCM test program.
2023-12-04 Added sample .WAV
2023-12-07 Fixed ROM-dump functionality of the Rescue IPL.
2023-12-07 Rescue IPL screen mode 31KHz 640x400.
2023-12-12 Experimental CDREAD program prints DMA current count after reading.
2024-01-14 Adding FDWRITE2 for writing D77/RDD file back to disk.
2024-01-15 Working on FDWRITE2
2024-01-15 Can format from .D77 image.
2024-01-15 Can write D77 disk back (at least in Tsugaru).
2024-01-15 Supporting RDD write-back.
2024-01-15 Can write BIN disk back (at least in Tsugaru).
2024-01-15 Reorganization.
2024-01-16 Added FDDUMP.EXP and FDWRITE2.EXP
2024-01-27 Sampled response to CDC CMD 1F|03 00 00 00 00 00 00 00 using real MX.
2024-03-06 Working on 386SX support.
2024-03-07 Patch UX's ROM IO.SYS bug.
2024-03-07 Experimental 386SX support seems to be working.
2024-03-07 FD IPL supports 386SX.
2024-03-07 IPL supports UX.
2024-03-10 Added TsugaruDebugBreak macro.
2024-03-11 Updated ICMWRITE for supporting 386SX.
2024-03-11 Disk BIOS device ID test.
2024-03-17 IPL checks timeout after SCSI_WAIT_READY. Increased timeout from 3ms to 30ms.
2024-03-17 Added Marty EX-ROM info (but not doing anything with it.)
2024-03-19 Interesting timer experiment.
2024-03-21 80387 TEST
2024-03-21 Working on FPU test.
2024-04-20 Correct interpretation of JSR []
2024-04-20 Bug fix.
2024-07-26 [AD-D15NE] README with BOM
2024-11-15 CDIPL transfer program.
2024-12-05 Corrected ICM CMOS Backup Address in 386SX environment.
2024-12-05 SCSI_COMMAND won't try if the machine ID is 4AH (Marty)
2025-06-06 More detailed instruction on how to patch RAIDEN for CD boot.
2025-08-03 Automated buid.
2025-08-03 Added D77 file.
2025-09-17 Added CDOPEN experimental program.
2025-09-17 Experimental SCSICD Open/Close commands
2025-09-18 SCSIOPEN.EXE and SCSICLOS.EXE confirmed to work. Not work on DOS6+EMM386 environment.
2025-09-22 Write to ICM twice. Hope it supports MRAM.
2025-09-23 Added a boot option to select enable/disable YSSCSICD on FD/HD boot. If TOWNS has a functioning internal CD, and using the Rescue IPL to reduce wear of the internal CD, this option may be useful.
2025-09-23 Commented out DOS6 patch patterns because I do not know how to patch DOS6 from IPL yet.
2025-11-09 Read Joystick for FM-7
2025-11-11 Made separate samples folder.
2025-11-14 Disk BIOS Redirector detects and erase a pattern of F-BASIC V3.0 Level 10 that destroys $FC80 by copying unused code. Now it can start without -install2 option.
2025-11-15 mainSubTfr.asm sample should be able to transfer to VRAM in FM-7 (using VRAM access flag).
2025-11-17 Fixed: RS232CTapeBIOS was adding extra bytes between files.
2025-11-17 SAVELOG command.
2025-11-18 Added LZSS decompressor example.
2025-11-28 RS232C Disk/Tape BIOS fully-passive operation.
2025-12-11 Kyukyoku Tiger for FM TOWNS CD-BIOS patch.
2026-01-20 Updating transpart.py
2026-01-22 Updated version number.
2026-01-22 Corrected the version number.
2026-01-24 Warn if a disc is in the internal CD drive when booting from a SCSI CD drive.
2026-02-01 Playing with the Item library.
2026-02-07 Updated Kyukoku Tiger Patch so that it ignores T_OAK2.EXE error check and can start even when CMOS RAM is lost or corrupted.
2026-02-14 Exhancing CD-Boot
2026-02-14 Support multipel SCSI CD drives in the boot menu.
2026-02-14 Cleaned the boot menu.
2026-02-20 Added FAST POWER-ON MEMORY TEST option in the CMOS Menu.
2026-02-25 Disabling the original CD-ROM BIOS when injecting YSSCSICD during boot.
2026-02-25 Updated IPL version number.
2026-02-25 Letting YSSCSICD.SYS patch RUN386.EXE to avoid I/O 4C0H DRY check.
2026-02-26 Patch RUN386.EXE to prevent it from directly beating CD-ROM I/O. Block R:\RUN386.EXE and force it to use Q:\RUN386.EXE.
2026-02-26 Correct Chase HQ patch. I updated document and forgot updating the patch itself.
2026-02-26 Fixed broken message.
2026-02-27 Added #include <string.h> in Kyukyoku Tiger patch.
2026-02-27 Added #include <string.h> in Rocket Ranger patch.
2026-03-01 Updated readme.
2026-03-05 c -> cpp
2026-03-05 Fix build with gcc.
2026-03-08 Adding messages in the SUBSTIPL
2026-03-08 Added WAIT_CD_READY
2026-03-08 Original-CDBIOS Disable Patch in subst IPL.
2026-03-08 Question: Do 386SX models load IPL from SCSI CD? It is known that 386SX models use its own IPL (sort of) in the SYSROM instead of the IPL written in the media.
2026-03-09 Reorganizing.
2026-03-09 Updated SUBSTIPL in the Galaxy Force II patch.
2026-03-21 XMRECV, XMSEND support COM1 to COM4.
2026-03-22 Replaced RS232C_STI, RS232C_CLI with inline.
2026-03-22 Tryed to add delay before and after accessing RS232C I/O, but still it crashes in the middle.
2026-03-23 Handle RxRDY INT.
2026-03-23 XMSEND, XMRECV improvements. Added help messages.
2026-03-23 XMRECV wait for 1 second, and then clear read buffer before retrying.\n
2026-03-26 Added SCSI Open/Close Lid functions.
2026-03-27 READ_PADA returns Run/Select status in b7 and b6.
2026-03-27 Call FD BIOS AH=0E before reading from Sector 0 of FD.
2026-03-27 Can Open/Close lid from BOOT MENU.
2026-03-27 Omitted TEST UNIT READY before sending SCSI open/close command.
2026-03-27 Added some more CMOS settings.
2026-03-27 Bug fix in case last-selected device has been removed from the system.
2026-03-28 Fixed pad-release problem.
2026-03-28 Trying different way of dealing with the chattering.
2026-03-29 Removed TASK.BAT for building IPL.
2026-03-30 Fixed Triple Confirmation before CMOS Reset.
2026-04-05 Made error message visible.
2026-04-15 Align entry address of LOADER with .COM. It starts from 8000:0100.
